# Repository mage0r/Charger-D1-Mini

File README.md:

Dual Source Charger for D1 Mini
=============
Currently seeking a new, flashier name.

This project is a dual power source charger that breaks out to 3.3v to power the D1 Mini.

The dual power circuit is mostly taken from https://github.com/CCHS-Melbourne/ESPlant

CREDITS
------------

This project was designed by [John Spencer](https://github.com/mage0r)
With a special thanks to [Angus Gratton](https://github.com/projectgus)

Made at hackmelbourne.org!

SPECIAL THANKS
------------

To the HackMelbourne (CCHS, http://hackmelbourne.org) community of Melbourne, Australia.

To all other open-source developers whose countless hours supported every other aspect of this design.

DISTRIBUTION
------------
The specific terms of distribution of this project are governed by the
license referenced below. Please contact the copyright owner if you wish to modify the board for distribution. Please utilize this design for personal or research projects. Please acknowledge all contributors.

LICENSE
-------
Licensed under the TAPR Open Hardware License (www.tapr.org/OHL).
The "license" sub-folder also contains a copy of this license in plain text format.

Copyright John Spencer, Angus Gratton 2016

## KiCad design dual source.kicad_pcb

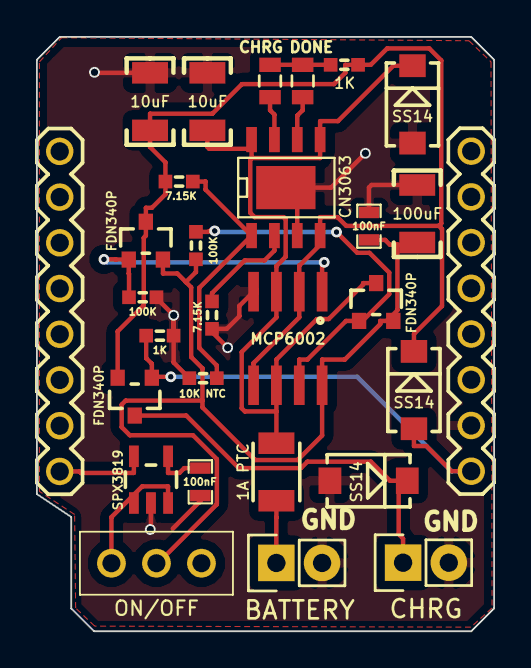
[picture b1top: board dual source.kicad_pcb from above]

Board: 2 copper layers, 25.4 x 33.0 mm, 29 parts (0 on the bottom side), 17 nets.

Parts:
C2, C202: 100nF; 0603_CAP
C201, C204: 10uF; 1210_CAP
C203: 100uF; 1210_CAP
D1, D2, D201: SS14; DIODE_SMA
F1: 1A PTC; 1210
LED201: DONE; 0805
LED202: CHRG; 0805
ON/OFF: ON/OFF; SS12D00
P1: BATTERY; Pin_Header_Straight_1x02
P2: CHRG; Pin_Header_Straight_1x02
P3, P4: CONN_01X08; 1X08
Q201, Q202, Q203: FDN340P; SOT23_FET
R4, R5: 100K; 0603
R201, R202: 1K; 0603
R204, R205: 7.15K; 0603
TH201: 10K NTC; 0603
U1: SPX3819; SOT23-5
U201: CN3063; CN3063_SOIC8_EP
U202: MCP6002; SO08_4mm

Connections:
+3V3: P3.8, U1.5
+5V: D201.A, P4.8, Q201.G, R201.1
/BAT+: F1.1, P1.1
/Power/GBAT: Q203.G, R5.2, U202.7
/Power/GIN: Q202.G, R4.1, U202.1
/Power/SOLAR_IN: D1.K, P2.1, Q201.D
/Power/VBAT: C204.1, D2.K, F1.2, Q203.D, U201.5, U201.8, U202.3, U202.6
/Power/VIN: C201.1, D201.K, Q201.S, Q202.D, R202.1, R205.1, U201.4, U202.2, U202.5
/Power/VOUT: C202.1, C203.2, ON/OFF.2, Q202.S, Q203.S, R5.1, U202.8
/Power/~CHRG: LED202.1, U201.7
/Power/~DONE: LED201.1, U201.6
/VOUT: ON/OFF.1, U1.1, U1.3
GND: C2.2, C201.2, C202.2, C203.1, C204.2, D1.A, D2.A, P1.2, P2.2, P4.7, R4.2, R201.2, R204.2, TH201.2, U1.2, U201.3, U201.PAD, U202.4
unnamed: C2.1, U1.4
unnamed: LED201.2, LED202.2, R202.2
unnamed: R204.1, U201.2
unnamed: R205.2, TH201.1, U201.1

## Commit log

2016-10-31 So, having complete gnd plane helps...
